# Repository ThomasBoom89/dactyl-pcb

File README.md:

# Custom PCB for dactyl split keyboard

## Keyboard without pcb holder

## Left PCB

## Right PCB

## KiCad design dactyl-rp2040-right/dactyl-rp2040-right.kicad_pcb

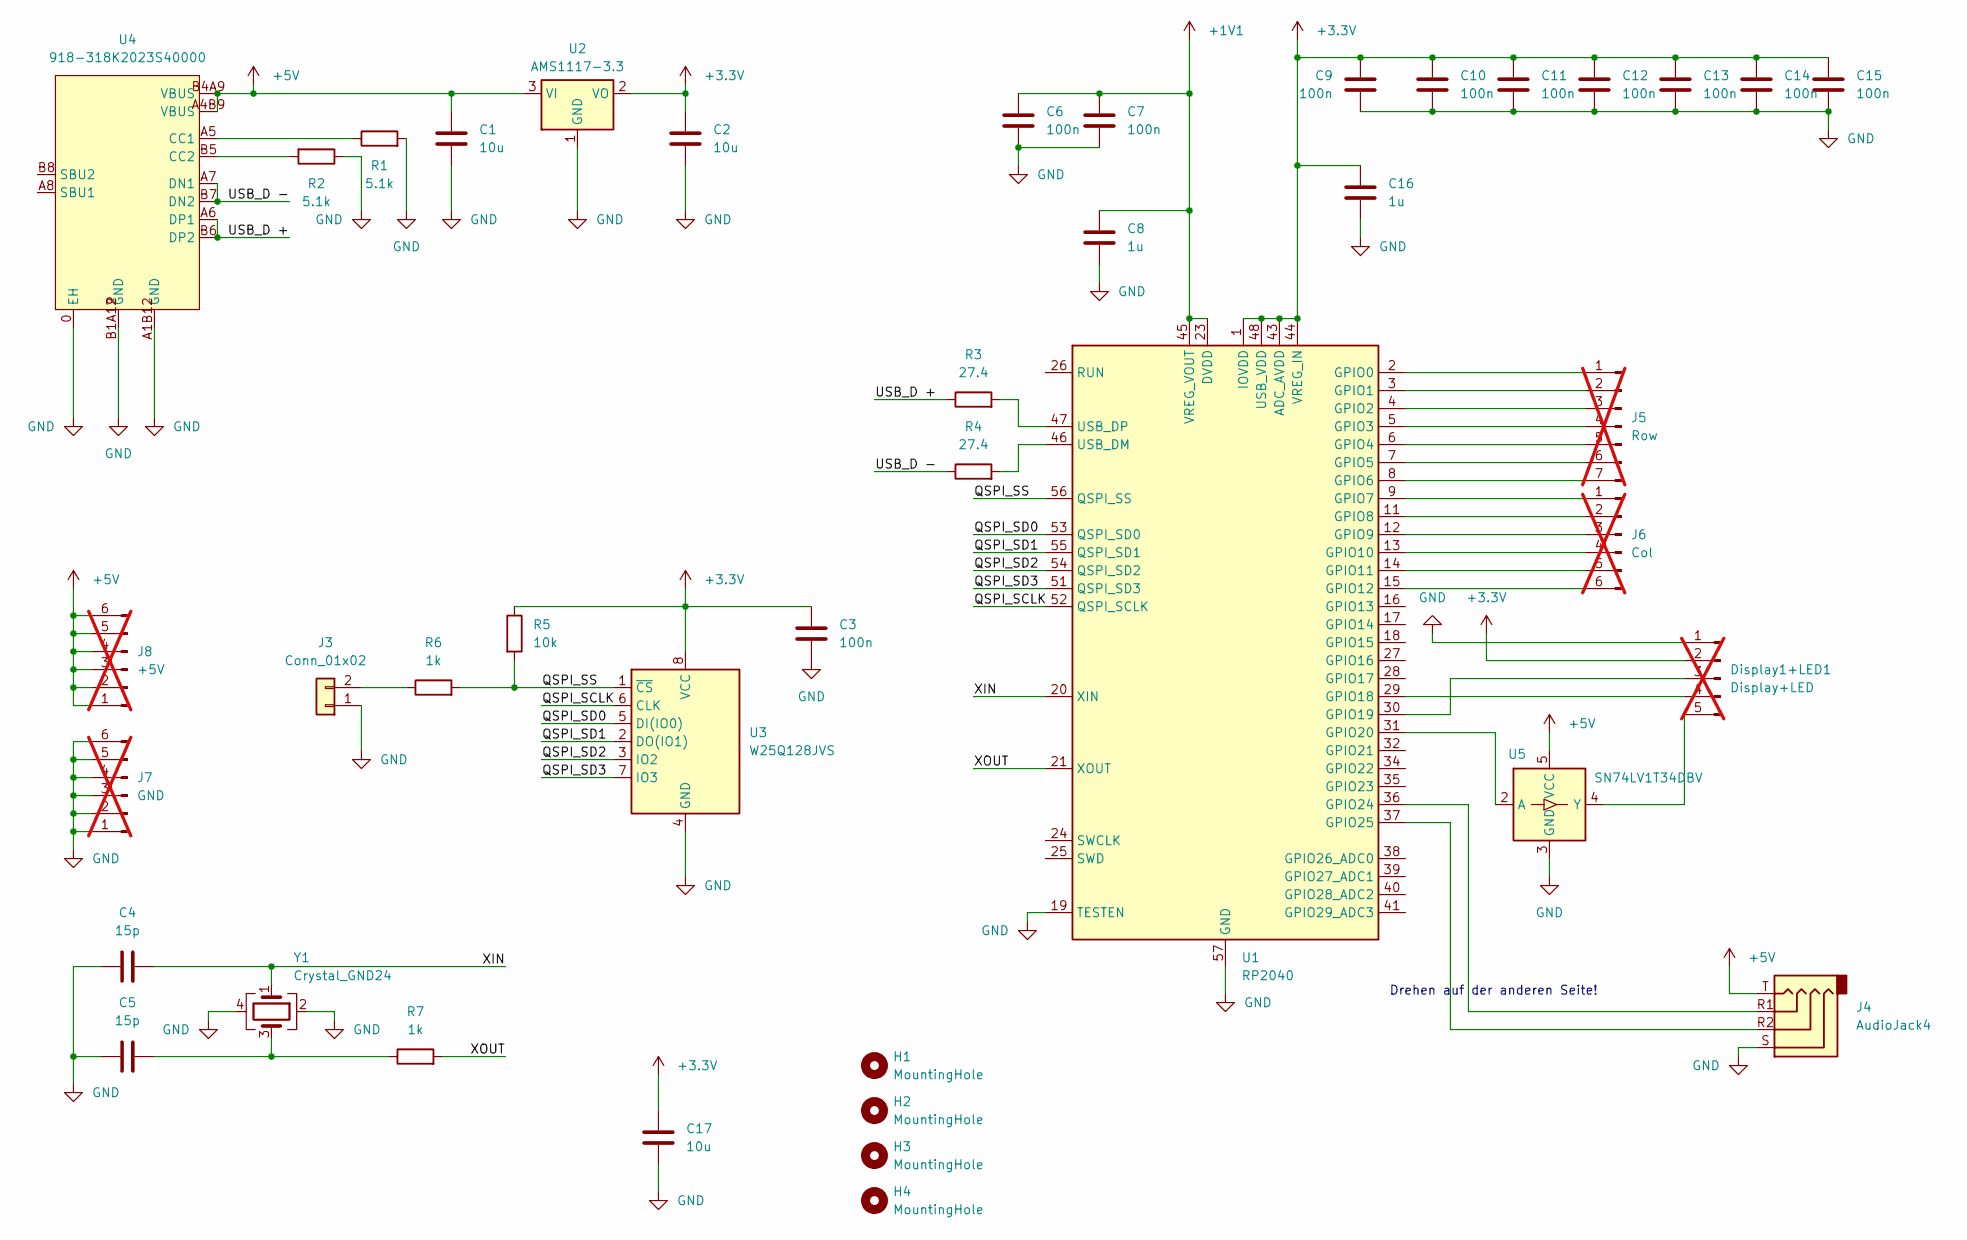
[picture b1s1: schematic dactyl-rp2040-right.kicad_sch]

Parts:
C1, C2, C17: 10u; C_0805_2012Metric_Pad1.18x1.45mm_HandSolder
C3, C7, C10, C11, C12, C13, C15: 100n; C_0603_1608Metric_Pad1.08x0.95mm_HandSolder
C4, C5: 15p; C_0603_1608Metric_Pad1.08x0.95mm_HandSolder
C6, C9, C14: 100n; C_0402_1005Metric_Pad0.74x0.62mm_HandSolder
C8, C16: 1u; C_0603_1608Metric_Pad1.08x0.95mm_HandSolder
Display1+LED1: Display+LED; JST_ZH_B5B-ZR_1x05_P1.50mm_Vertical; not fitted
H1, H2, H3, H4: MountingHole; MountingHole_2.7mm_M2.5
J3: Conn_01x02; PinHeader_1x02_P2.54mm_Vertical
J4: AudioJack4; Jack_3.5mm_PJ320E_Horizontal
J5: Row; JST_ZH_B7B-ZR_1x07_P1.50mm_Vertical; not fitted
J6: Col; JST_ZH_B6B-ZR_1x06_P1.50mm_Vertical; not fitted
J7: GND; JST_ZH_B6B-ZR_1x06_P1.50mm_Vertical; not fitted
J8: +5V; JST_ZH_B6B-ZR_1x06_P1.50mm_Vertical; not fitted
R1, R2: 5.1k; R_0805_2012Metric_Pad1.20x1.40mm_HandSolder
R3, R4: 27.4; R_0402_1005Metric_Pad0.72x0.64mm_HandSolder
R5: 10k; R_0603_1608Metric_Pad0.98x0.95mm_HandSolder
R6, R7: 1k; R_0603_1608Metric_Pad0.98x0.95mm_HandSolder
U1: RP2040; RP2040-QFN-56
U2: AMS1117-3.3; SOT-223-3_TabPin2
U3: W25Q128JVS; SOIC-8_5.23x5.23mm_P1.27mm
U4: 918-318K2023S40000; USB-C-SMD_918-318K2023S40000; LCSC Part C19189945
U5: SN74LV1T34DBV; SOT-23-5
Y1: Crystal_GND24; Crystal_SMD_3225-4Pin_3.2x2.5mm

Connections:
+1V1: C6.1, C7.1, C8.1, U1.23 (DVDD), U1.45 (VREG_VOUT), U1.50 (DVDD)
+3.3V: C2.1, C3.1, C9.1, C10.1, C11.1, C12.1, C13.1, C14.1, C15.1, C16.1, C17.1, Display1+LED1.2, R5.1, U1.1 (IOVDD), U1.10 (IOVDD), U1.22 (IOVDD), U1.33 (IOVDD), U1.42 (IOVDD), U1.43 (ADC_AVDD), U1.44 (VREG_IN), U1.48 (USB_VDD), U1.49 (IOVDD), U2.2 (VO), U3.8 (VCC)
+5V: C1.1, J4.T, J8.1, J8.2, J8.3, J8.4, J8.5, J8.6, U2.3 (VI), U4.A4B9 (VBUS), U4.B4A9 (VBUS), U5.5 (VCC)
/QSPI_SCLK: U1.52 (QSPI_SCLK), U3.6 (CLK)
/QSPI_SD0: U1.53 (QSPI_SD0), U3.5 (DI(IO0))
/QSPI_SD1: U1.55 (QSPI_SD1), U3.2 (DO(IO1))
/QSPI_SD2: U1.54 (QSPI_SD2), U3.3 (IO2)
/QSPI_SD3: U1.51 (QSPI_SD3), U3.7 (IO3)
/QSPI_SS: R5.2, R6.2, U1.56 (QSPI_SS), U3.1 (~CS)
/USB_D +: R3.1, U4.A6 (DP1), U4.B6 (DP2)
/USB_D -: R4.1, U4.A7 (DN1), U4.B7 (DN2)
/XIN: C4.1, U1.20 (XIN), Y1.1
/XOUT: R7.2, U1.21 (XOUT)
GND: C1.2, C2.2, C3.2, C4.2, C5.1, C6.2, C7.2, C8.2, C9.2, C10.2, C11.2, C12.2, C13.2, C14.2, C15.2, C16.2, C17.2, Display1+LED1.1, J3.1, J4.S, J7.1, J7.2, J7.3, J7.4, J7.5, J7.6, R1.2, R2.1, U1.19 (TESTEN), U1.57 (GND), U2.1 (GND), U3.4 (GND), U4.0 (EH), U4.A1B12 (GND), U4.B1A12 (GND), U5.3 (GND), Y1.2, Y1.4
unnamed: C5.2, R7.1, Y1.3
unnamed: Display1+LED1.3, U1.30 (GPIO19)
unnamed: Display1+LED1.4, U1.29 (GPIO18)
unnamed: Display1+LED1.5, U5.4 (Y)
unnamed: J3.2, R6.1
unnamed: J5.1, U1.2 (GPIO0)
unnamed: J5.2, U1.3 (GPIO1)
unnamed: J5.3, U1.4 (GPIO2)
unnamed: J5.4, U1.5 (GPIO3)
unnamed: J5.5, U1.6 (GPIO4)
unnamed: J5.6, U1.7 (GPIO5)
unnamed: J5.7, U1.8 (GPIO6)
unnamed: J6.1, U1.9 (GPIO7)
unnamed: J6.2, U1.11 (GPIO8)
unnamed: J6.3, U1.12 (GPIO9)
unnamed: J6.4, U1.13 (GPIO10)
unnamed: J6.5, U1.14 (GPIO11)
unnamed: J6.6, U1.15 (GPIO12)
unnamed: U1.31 (GPIO20), U5.2 (A)
unnamed: J4.R1, U1.36 (GPIO24)
unnamed: J4.R2, U1.37 (GPIO25)
unnamed: R4.2, U1.46 (USB_DM)
unnamed: R3.2, U1.47 (USB_DP)
unnamed: R1.1, U4.A5 (CC1)
unnamed: R2.2, U4.B5 (CC2)

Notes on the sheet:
Drehen auf der anderen Seite!

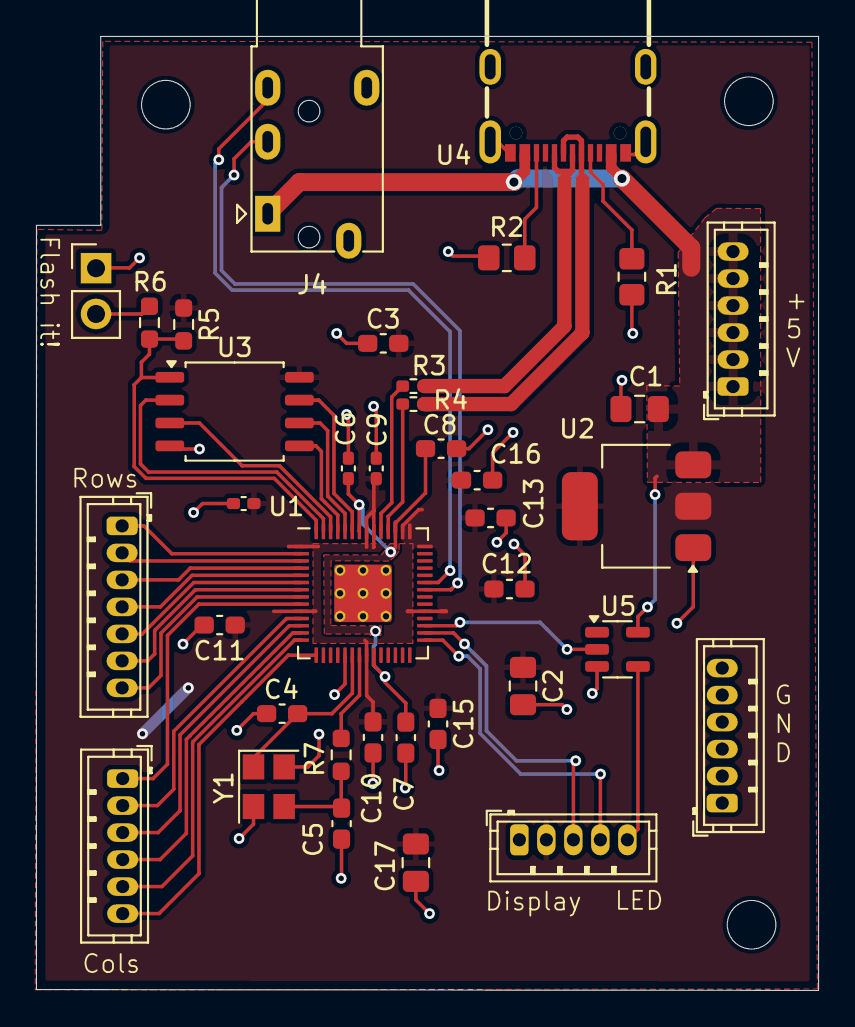
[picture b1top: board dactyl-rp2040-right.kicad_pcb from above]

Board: 2 copper layers, 43.4 x 53.0 mm, 40 parts (0 on the bottom side), 39 nets.

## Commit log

2025-03-24 Initial commit :tada:
